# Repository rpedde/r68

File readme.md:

# r68 std #

This a 68% board, like a tada or sabre.

This supports two layouts:

[Compat](https://goo.gl/bRej9A): This format requires a 1.75u right shift, but retains 1.25u FN keys ([json data](compat.json))

[Narrow](https://goo.gl/9U5wPm): This keeps more meta keys to the right of the space bar, but requires 1u FN keys ([json data](narrow.json))

## Hardware Revisions/Errata ##

* 1.0: Initial version (bad right arrow, not recommended) [gerbers](https://storage.googleapis.com/rpedde-public-gerbers/r68-r1.0.zip)
* 1.1: Fix right arrow, change (ground short on C14) [gerbers](https://storage.googleapis.com/rpedde-public-gerbers/r68-r1.1.zip)
* 1.2: Repour ground (ordered from easyeda, verified working) [gerbers](https://storage.googleapis.com/rpedde-public-gerbers/r68-r1.2.zip)

## License ##

This work is Copyright 2017 Ron Pedde and distributed under the term of the GNU General Public License (version 2 or later).

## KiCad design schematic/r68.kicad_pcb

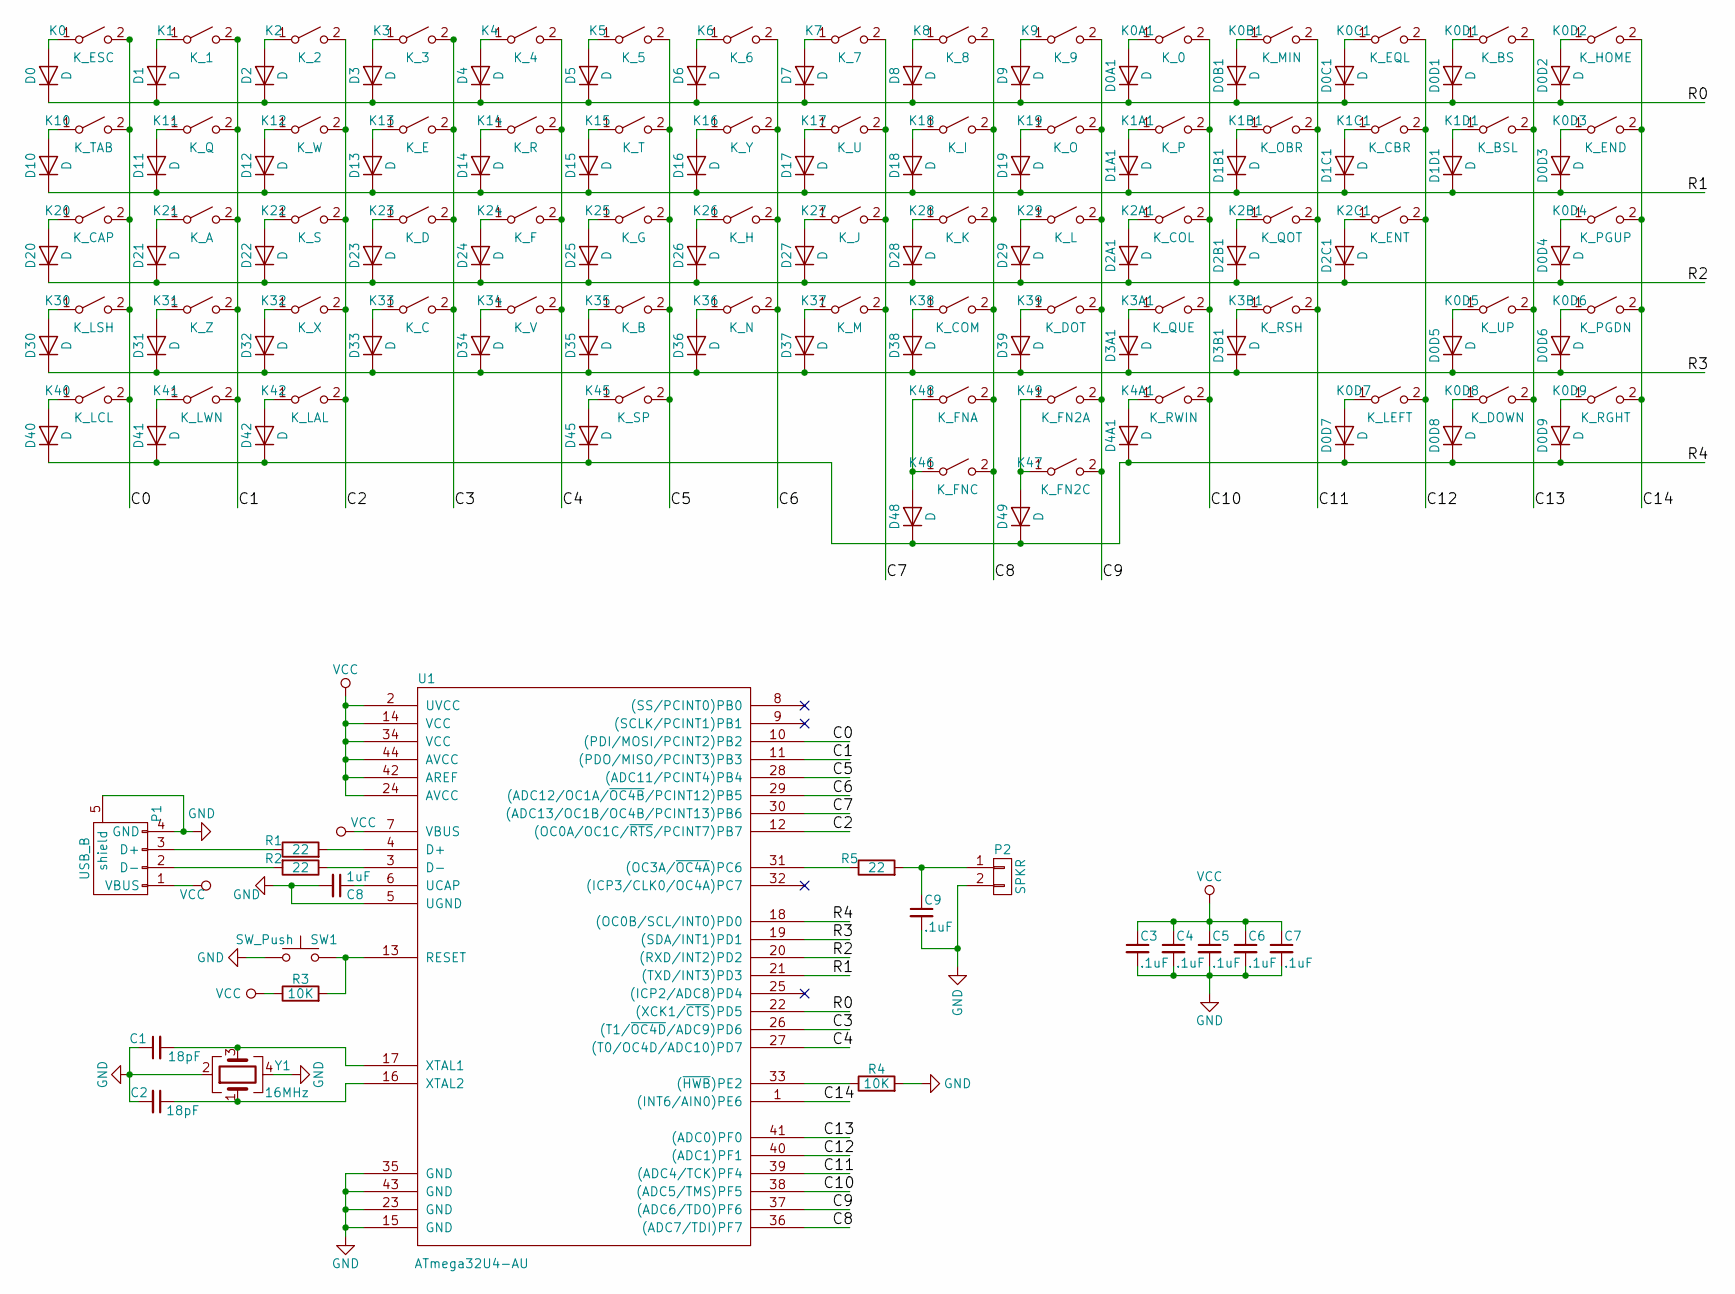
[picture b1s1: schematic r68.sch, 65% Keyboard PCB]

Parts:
C1, C2: 18pF; C_0805
C3, C4, C5, C6, C7, C9: .1uF; C_0805
C8: 1uF; C_0805
D0, D0A1, D0B1, D0C1, D0D1, D0D2, D0D3, D0D4, D0D5, D0D6, D0D7, D0D8, D0D9, D1, D1A1, D1B1, D1C1, D1D1, D2, D2A1, D2B1, D2C1, D3, D3A1, D3B1, D4, D4A1, D5, D6, D7, D8, D9, D10, D11, D12, D13, D14, D15, D16, D17, D18, D19, D20, D21, D22, D23, D24, D25, D26, D27, D28, D29, D30, D31, D32, D33, D34, D35, D36, D37, D38, D39, D40, D41, D42, D45, D48, D49: D; D_0805
K0: K_ESC; CHERRY_PCB_100H
K0A1: K_0; CHERRY_PCB_100H
K0B1: K_MIN; CHERRY_PCB_100H
K0C1: K_EQL; CHERRY_PCB_100H
K0D1: K_BS; CHERRY_PCB_200H
K0D2: K_HOME; CHERRY_PCB_100H
K0D3: K_END; CHERRY_PCB_100H
K0D4: K_PGUP; CHERRY_PCB_100H
K0D5: K_UP; CHERRY_PCB_100H
K0D6: K_PGDN; CHERRY_PCB_100H
K0D7: K_LEFT; CHERRY_PCB_100H
K0D8: K_DOWN; CHERRY_PCB_100H
K0D9: K_RGHT; CHERRY_PCB_100H
K1: K_1; CHERRY_PCB_100H
K1A1: K_P; CHERRY_PCB_100H
K1B1: K_OBR; CHERRY_PCB_100H
K1C1: K_CBR; CHERRY_PCB_100H
K1D1: K_BSL; CHERRY_PCB_150H
K2: K_2; CHERRY_PCB_100H
K2A1: K_COL; CHERRY_PCB_100H
K2B1: K_QOT; CHERRY_PCB_100H
K2C1: K_ENT; CHERRY_PCB_225H
K3: K_3; CHERRY_PCB_100H
K3A1: K_QUE; CHERRY_PCB_100H
K3B1: K_RSH; CHERRY_PCB_175H
K4: K_4; CHERRY_PCB_100H
K4A1: K_RWIN; CHERRY_PCB_100H
K5: K_5; CHERRY_PCB_100H
K6: K_6; CHERRY_PCB_100H
K7: K_7; CHERRY_PCB_100H
K8: K_8; CHERRY_PCB_100H
K9: K_9; CHERRY_PCB_100H
K10: K_TAB; CHERRY_PCB_150H
K11: K_Q; CHERRY_PCB_100H
K12: K_W; CHERRY_PCB_100H
K13: K_E; CHERRY_PCB_100H
K14: K_R; CHERRY_PCB_100H
K15: K_T; CHERRY_PCB_100H
K16: K_Y; CHERRY_PCB_100H
K17: K_U; CHERRY_PCB_100H
K18: K_I; CHERRY_PCB_100H
K19: K_O; CHERRY_PCB_100H
K20: K_CAP; CHERRY_PCB_175H
K21: K_A; CHERRY_PCB_100H
K22: K_S; CHERRY_PCB_100H
K23: K_D; CHERRY_PCB_100H
K24: K_F; CHERRY_PCB_100H
K25: K_G; CHERRY_PCB_100H
K26: K_H; CHERRY_PCB_100H
K27: K_J; CHERRY_PCB_100H
K28: K_K; CHERRY_PCB_100H
K29: K_L; CHERRY_PCB_100H
K30: K_LSH; CHERRY_PCB_225H
K31: K_Z; CHERRY_PCB_100H
K32: K_X; CHERRY_PCB_100H
K33: K_C; CHERRY_PCB_100H
K34: K_V; CHERRY_PCB_100H
K35: K_B; CHERRY_PCB_100H
K36: K_N; CHERRY_PCB_100H
K37: K_M; CHERRY_PCB_100H
K38: K_COM; CHERRY_PCB_100H
K39: K_DOT; CHERRY_PCB_100H
K40: K_LCL; CHERRY_PCB_125H
K41: K_LWN; CHERRY_PCB_125H
K42: K_LAL; CHERRY_PCB_125H
K45: K_SP; CHERRY_PCB_625H
K46: K_FNC; CHERRY_PCB_100H
K47: K_FN2C; CHERRY_PCB_100H
K48: K_FNA; CHERRY_PCB_125H
K49: K_FN2A; CHERRY_PCB_125H
P1: USB_B; USB_Mini-B
P2: SPKR; Pin_Header_Straight_1x02_Pitch2.54mm
R1, R2, R5: 22; R_0805
R3, R4: 10K; R_0805
SW1: SW_Push; SW_SPST_TL3342
U1: ATmega32U4-AU; TQFP-44_10x10mm_Pitch0.8mm
Y1: 16MHz; Crystal_SMD_3225-4pin_3.2x2.5mm

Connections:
/C0: K0.2 (B), K10.2 (B), K20.2 (B), K30.2 (B), K40.2 (B), U1.10 ((PDI/MOSI/PCINT2)PB2)
/C1: K1.2 (B), K11.2 (B), K21.2 (B), K31.2 (B), K41.2 (B), U1.11 ((PDO/MISO/PCINT3)PB3)
/C2: K2.2 (B), K12.2 (B), K22.2 (B), K32.2 (B), K42.2 (B), U1.12 ((OC0A/OC1C/~RTS~/PCINT7)PB7)
/C3: K3.2 (B), K13.2 (B), K23.2 (B), K33.2 (B), U1.26 ((T1/~OC4D~/ADC9)PD6)
/C4: K4.2 (B), K14.2 (B), K24.2 (B), K34.2 (B), U1.27 ((T0/OC4D/ADC10)PD7)
/C5: K5.2 (B), K15.2 (B), K25.2 (B), K35.2 (B), K45.2 (B), U1.28 ((ADC11/PCINT4)PB4)
/C6: K6.2 (B), K16.2 (B), K26.2 (B), K36.2 (B), U1.29 ((ADC12/OC1A/~OC4B~/PCINT12)PB5)
/C7: K7.2 (B), K17.2 (B), K27.2 (B), K37.2 (B), U1.30 ((ADC13/OC1B/OC4B/PCINT13)PB6)
/C8: K8.2 (B), K18.2 (B), K28.2 (B), K38.2 (B), K46.2 (B), K48.2 (B), U1.36 ((ADC7/TDI)PF7)
/C9: K9.2 (B), K19.2 (B), K29.2 (B), K39.2 (B), K47.2 (B), K49.2 (B), U1.37 ((ADC6/TDO)PF6)
/C10: K0A1.2 (B), K1A1.2 (B), K2A1.2 (B), K3A1.2 (B), K4A1.2 (B), U1.38 ((ADC5/TMS)PF5)
/C11: K0B1.2 (B), K1B1.2 (B), K2B1.2 (B), K3B1.2 (B), U1.39 ((ADC4/TCK)PF4)
/C12: K0C1.2 (B), K0D7.2 (B), K1C1.2 (B), K2C1.2 (B), U1.40 ((ADC1)PF1)
/C13: K0D1.2 (B), K0D5.2 (B), K0D8.2 (B), K1D1.2 (B), U1.41 ((ADC0)PF0)
/C14: K0D2.2 (B), K0D3.2 (B), K0D4.2 (B), K0D6.2 (B), K0D9.2 (B), U1.1 ((INT6/AIN0)PE6)
/R0: D0.1 (K), D0A1.1 (K), D0B1.1 (K), D0C1.1 (K), D0D1.1 (K), D0D2.1 (K), D1.1 (K), D2.1 (K), D3.1 (K), D4.1 (K), D5.1 (K), D6.1 (K), D7.1 (K), D8.1 (K), D9.1 (K), U1.22 ((XCK1/~CTS~)PD5)
/R1: D0D3.1 (K), D1A1.1 (K), D1B1.1 (K), D1C1.1 (K), D1D1.1 (K), D10.1 (K), D11.1 (K), D12.1 (K), D13.1 (K), D14.1 (K), D15.1 (K), D16.1 (K), D17.1 (K), D18.1 (K), D19.1 (K), U1.21 ((TXD/INT3)PD3)
/R2: D0D4.1 (K), D2A1.1 (K), D2B1.1 (K), D2C1.1 (K), D20.1 (K), D21.1 (K), D22.1 (K), D23.1 (K), D24.1 (K), D25.1 (K), D26.1 (K), D27.1 (K), D28.1 (K), D29.1 (K), U1.20 ((RXD/INT2)PD2)
/R3: D0D5.1 (K), D0D6.1 (K), D3A1.1 (K), D3B1.1 (K), D30.1 (K), D31.1 (K), D32.1 (K), D33.1 (K), D34.1 (K), D35.1 (K), D36.1 (K), D37.1 (K), D38.1 (K), D39.1 (K), U1.19 ((SDA/INT1)PD1)
/R4: D0D7.1 (K), D0D8.1 (K), D0D9.1 (K), D4A1.1 (K), D40.1 (K), D41.1 (K), D42.1 (K), D45.1 (K), D48.1 (K), D49.1 (K), U1.18 ((OC0B/SCL/INT0)PD0)
GND: C1.1, C2.2, C3.2, C4.2, C5.2, C6.2, C7.2, C8.2, C9.2, P1.4 (GND), P1.5 (shield), P2.2, R4.2, SW1.1, U1.5 (UGND), U1.15 (GND), U1.23 (GND), U1.35 (GND), U1.43 (GND), Y1.2, Y1.4
unnamed: C1.2, U1.17 (XTAL1), Y1.3
unnamed: C2.1, U1.16 (XTAL2), Y1.1
unnamed: C8.1, U1.6 (UCAP)
unnamed: C9.1, P2.1, R5.2
unnamed: D0.2 (A), K0.1 (A)
unnamed: D0A1.2 (A), K0A1.1 (A)
unnamed: D0B1.2 (A), K0B1.1 (A)
unnamed: D0C1.2 (A), K0C1.1 (A)
unnamed: D0D1.2 (A), K0D1.1 (A)
unnamed: D0D2.2 (A), K0D2.1 (A)
unnamed: D0D3.2 (A), K0D3.1 (A)
unnamed: D0D4.2 (A), K0D4.1 (A)
unnamed: D0D5.2 (A), K0D5.1 (A)
unnamed: D0D6.2 (A), K0D6.1 (A)
unnamed: D0D7.2 (A), K0D7.1 (A)
unnamed: D0D8.2 (A), K0D8.1 (A)
unnamed: D0D9.2 (A), K0D9.1 (A)
unnamed: D1.2 (A), K1.1 (A)
unnamed: D1A1.2 (A), K1A1.1 (A)
unnamed: D1B1.2 (A), K1B1.1 (A)
unnamed: D1C1.2 (A), K1C1.1 (A)
unnamed: D1D1.2 (A), K1D1.1 (A)
unnamed: D2.2 (A), K2.1 (A)
unnamed: D2A1.2 (A), K2A1.1 (A)
unnamed: D2B1.2 (A), K2B1.1 (A)
unnamed: D2C1.2 (A), K2C1.1 (A)
unnamed: D3.2 (A), K3.1 (A)
unnamed: D3A1.2 (A), K3A1.1 (A)
unnamed: D3B1.2 (A), K3B1.1 (A)
unnamed: D4.2 (A), K4.1 (A)
unnamed: D4A1.2 (A), K4A1.1 (A)
unnamed: D5.2 (A), K5.1 (A)
unnamed: D6.2 (A), K6.1 (A)
unnamed: D7.2 (A), K7.1 (A)
unnamed: D8.2 (A), K8.1 (A)
unnamed: D9.2 (A), K9.1 (A)
unnamed: D10.2 (A), K10.1 (A)
unnamed: D11.2 (A), K11.1 (A)
unnamed: D12.2 (A), K12.1 (A)
unnamed: D13.2 (A), K13.1 (A)
unnamed: D14.2 (A), K14.1 (A)
unnamed: D15.2 (A), K15.1 (A)
unnamed: D16.2 (A), K16.1 (A)
unnamed: D17.2 (A), K17.1 (A)
unnamed: D18.2 (A), K18.1 (A)
unnamed: D19.2 (A), K19.1 (A)
unnamed: D20.2 (A), K20.1 (A)
unnamed: D21.2 (A), K21.1 (A)
unnamed: D22.2 (A), K22.1 (A)
unnamed: D23.2 (A), K23.1 (A)
unnamed: D24.2 (A), K24.1 (A)
unnamed: D25.2 (A), K25.1 (A)
unnamed: D26.2 (A), K26.1 (A)
unnamed: D27.2 (A), K27.1 (A)
unnamed: D28.2 (A), K28.1 (A)
unnamed: D29.2 (A), K29.1 (A)
unnamed: D30.2 (A), K30.1 (A)
unnamed: D31.2 (A), K31.1 (A)
unnamed: D32.2 (A), K32.1 (A)
unnamed: D33.2 (A), K33.1 (A)
unnamed: D34.2 (A), K34.1 (A)
unnamed: D35.2 (A), K35.1 (A)
unnamed: D36.2 (A), K36.1 (A)
unnamed: D37.2 (A), K37.1 (A)
unnamed: D38.2 (A), K38.1 (A)
unnamed: D39.2 (A), K39.1 (A)
unnamed: D40.2 (A), K40.1 (A)
unnamed: D41.2 (A), K41.1 (A)
unnamed: D42.2 (A), K42.1 (A)
unnamed: D45.2 (A), K45.1 (A)
unnamed: D48.2 (A), K46.1 (A), K48.1 (A)
unnamed: D49.2 (A), K47.1 (A), K49.1 (A)
unnamed: P1.2 (D-), R2.2
unnamed: P1.3 (D+), R1.1
unnamed: R1.2, U1.4 (D+)
unnamed: R2.1, U1.3 (D-)
unnamed: R3.2, SW1.2, U1.13 (RESET)
unnamed: R4.1, U1.33 ((~HWB~)PE2)
unnamed: R5.1, U1.31 ((OC3A/~OC4A~)PC6)
VCC: C3.1, C4.1, C5.1, C6.1, C7.1, P1.1 (VBUS), R3.1, U1.2 (UVCC), U1.7 (VBUS), U1.14 (VCC), U1.24 (AVCC), U1.34 (VCC), U1.42 (AREF), U1.44 (AVCC)

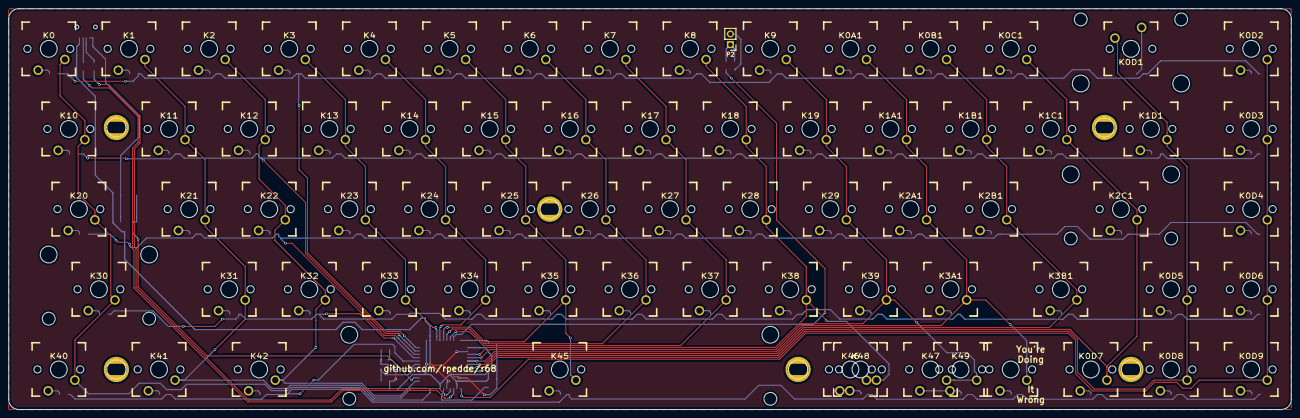
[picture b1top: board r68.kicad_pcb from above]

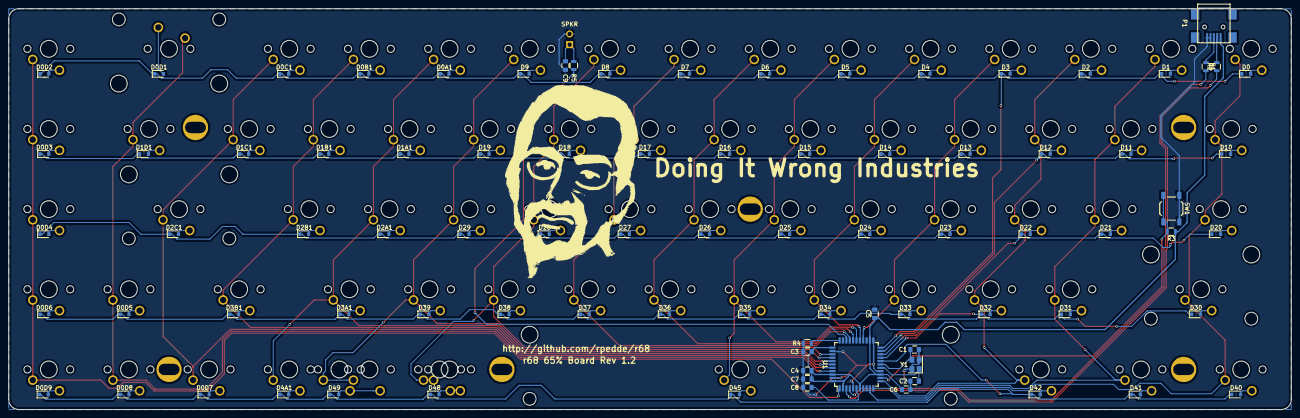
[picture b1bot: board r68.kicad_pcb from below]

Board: 2 copper layers, 304.8 x 95.3 mm, 157 parts (86 on the bottom side), 101 nets.

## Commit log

2017-10-05 initial checkin
2017-10-05 route for 68 key
2017-10-24 final hole placement and routing
2017-10-24 gitignore
2017-11-16 Minor fixes
    * fix right arrow that wasn't wired to r4
    * change the diode footprint to 0805
2017-11-24 fix shorted C14
2017-11-24 fix readme
2017-12-16 Add firmware
    Additionally, update the readme to indicate that r1.2 has been tested
    successfully.
2017-12-16 add licensing information
2018-05-05 make pictures match keymap
2018-05-05 fix keymap drawing
2019-09-28 add a LICENSE file in addition to COPYING
